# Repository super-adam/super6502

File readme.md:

## 
 - WinCUPL II v1.0 Beta 04/08/2025 (gal-glue-logic folder)
 - KiCad v9.0.6 (kicad folder)
 - KickAssembler v5.25 (src folder)

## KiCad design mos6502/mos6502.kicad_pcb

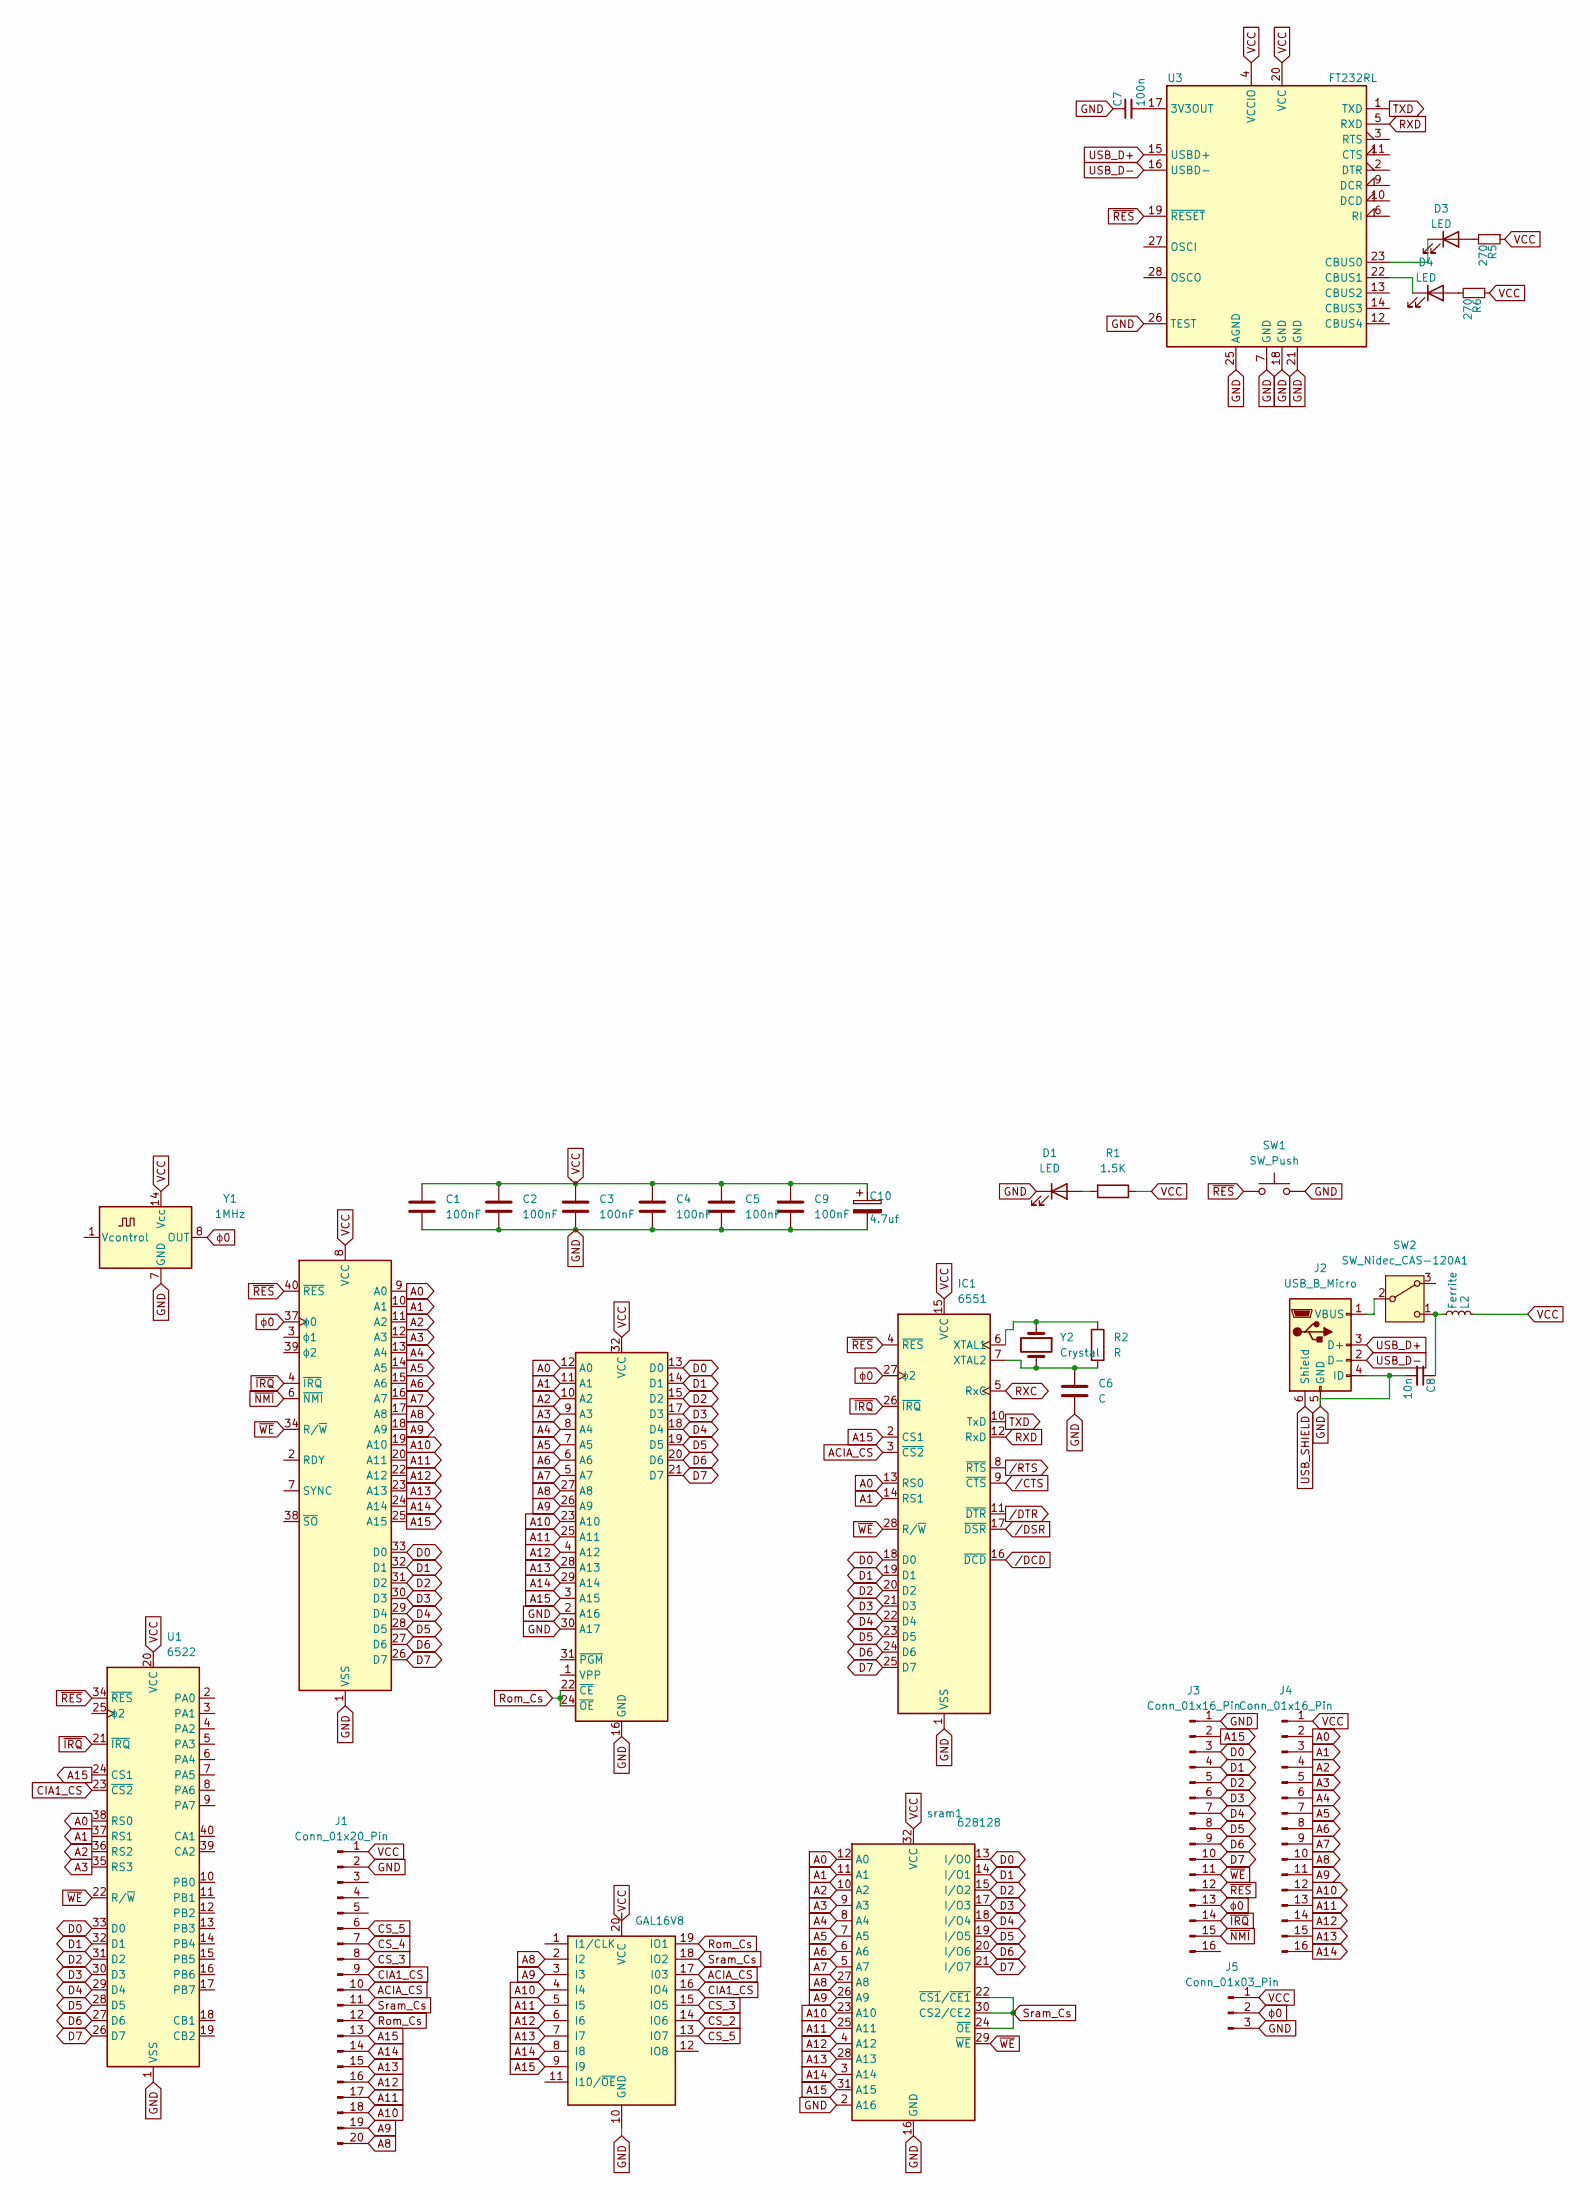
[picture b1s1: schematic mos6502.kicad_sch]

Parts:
C1, C2, C3, C4, C5, C9: 100nF; C_Disc_D5.0mm_W2.5mm_P2.50mm
C6: C; C_0805_2012Metric_Pad1.18x1.45mm_HandSolder
C7: 100n; C_0603_1608Metric
C8: 10n; C_0603_1608Metric
C10: 4.7uf; C_0603_1608Metric
D1: LED; LED_D3.0mm
D3, D4: LED; LED_0805_2012Metric_Pad1.15x1.40mm_HandSolder
IC1: 6551; DIP-28_W15.24mm
J1: Conn_01x20_Pin; PinHeader_1x20_P2.54mm_Vertical
J2: USB_B_Micro; Conn_USBmicro-B_ebay-side_TH
J3, J4: Conn_01x16_Pin; PinHeader_1x16_P2.54mm_Vertical
J5: Conn_01x03_Pin; PinHeader_1x03_P2.54mm_Vertical
L2: Ferrite; L_0603_1608Metric
R1: 1.5K; R_Axial_DIN0207_L6.3mm_D2.5mm_P2.54mm_Vertical
R2: R; R_0805_2012Metric_Pad1.20x1.40mm_HandSolder
R5, R6: 270; R_0603_1608Metric
SW1: SW_Push; SW_Tactile_SKHH_Angled
SW2: SW_Nidec_CAS-120A1; SW_Slide_SPDT_Angled_CK_OS102011MA1Q
U1: 6522; DIP-40_W15.24mm
U3: FT232RL; SSOP-28_5.3x10.2mm_P0.65mm
Y1: 1MHz; Oscillator_DIP-14
Y2: Crystal; Crystal_HC18-U_Vertical
gal1: GAL16V8; DIP-20_W7.62mm
mos1: 6502; DIP-40_W15.24mm
rom1: 27C020; DIP-32_W15.24mm
sram1: 628128; DIP-32_W15.24mm

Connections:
A0: IC1.13 (RS0), J4.2, U1.38 (RS0), mos1.9 (A0), rom1.12 (A0), sram1.12 (A0)
A1: IC1.14 (RS1), J4.3, U1.37 (RS1), mos1.10 (A1), rom1.11 (A1), sram1.11 (A1)
A2: J4.4, U1.36 (RS2), mos1.11 (A2), rom1.10 (A2), sram1.10 (A2)
A3: J4.5, U1.35 (RS3), mos1.12 (A3), rom1.9 (A3), sram1.9 (A3)
A4: J4.6, mos1.13 (A4), rom1.8 (A4), sram1.8 (A4)
A5: J4.7, mos1.14 (A5), rom1.7 (A5), sram1.7 (A5)
A6: J4.8, mos1.15 (A6), rom1.6 (A6), sram1.6 (A6)
A7: J4.9, mos1.16 (A7), rom1.5 (A7), sram1.5 (A7)
A8: J1.20, J4.10, gal1.2 (I2), mos1.17 (A8), rom1.27 (A8), sram1.27 (A8)
A9: J1.19, J4.11, gal1.3 (I3), mos1.18 (A9), rom1.26 (A9), sram1.26 (A9)
A10: J1.18, J4.12, gal1.4 (I4), mos1.19 (A10), rom1.23 (A10), sram1.23 (A10)
A11: J1.17, J4.13, gal1.5 (I5), mos1.20 (A11), rom1.25 (A11), sram1.25 (A11)
A12: J1.16, J4.14, gal1.6 (I6), mos1.22 (A12), rom1.4 (A12), sram1.4 (A12)
A13: J1.15, J4.15, gal1.7 (I7), mos1.23 (A13), rom1.28 (A13), sram1.28 (A13)
A14: J1.14, J4.16, gal1.8 (I8), mos1.24 (A14), rom1.29 (A14), sram1.3 (A14)
A15: IC1.2 (CS1), J1.13, J3.2, U1.24 (CS1), gal1.9 (I9), mos1.25 (A15), rom1.3 (A15), sram1.31 (A15)
ACIA_CS: IC1.3 (~CS2), J1.10, gal1.17 (I03)
CIA1_CS: J1.9, U1.23 (~CS2), gal1.16 (IO4)
CS_2: gal1.14 (IO6)
CS_3: J1.8, gal1.15 (IO5)
CS_4: J1.7
CS_5: J1.6, gal1.13 (IO7)
D0: IC1.18 (D0), J3.3, U1.33 (D0), mos1.33 (D0), rom1.13 (D0), sram1.13 (I/O0)
D1: IC1.19 (D1), J3.4, U1.32 (D1), mos1.32 (D1), rom1.14 (D1), sram1.14 (I/O1)
D2: IC1.20 (D2), J3.5, U1.31 (D2), mos1.31 (D2), rom1.15 (D2), sram1.15 (I/O2)
D3: IC1.21 (D3), J3.6, U1.30 (D3), mos1.30 (D3), rom1.17 (D3), sram1.17 (I/O3)
D4: IC1.22 (D4), J3.7, U1.29 (D4), mos1.29 (D4), rom1.18 (D4), sram1.18 (I/O4)
D5: IC1.23 (D5), J3.8, U1.28 (D5), mos1.28 (D5), rom1.19 (D5), sram1.19 (I/O5)
D6: IC1.24 (D6), J3.9, U1.27 (D6), mos1.27 (D6), rom1.20 (D6), sram1.20 (I/O6)
D7: IC1.25 (D7), J3.10, U1.26 (D7), mos1.26 (D7), rom1.21 (D7), sram1.21 (I/O7)
GND: C1.2, C2.2, C3.2, C4.2, C5.2, C6.2, C7.1, C8.2, C9.2, C10.2, D1.1 (K), IC1.1 (VSS), J1.2, J2.4 (ID), J2.5 (GND), J3.1, J5.3, SW1.2, U1.1 (VSS), U3.7 (GND), U3.18 (GND), U3.21 (GND), U3.25 (AGND), U3.26 (TEST), Y1.7 (GND), gal1.10 (GND), mos1.1 (VSS), mos1.21 (VSS), rom1.2 (A16), rom1.16 (GND), rom1.30 (A17), sram1.2 (A16), sram1.16 (GND)
unnamed: D1.2 (A), R1.2
unnamed: D3.2 (A), R5.2
unnamed: D3.1 (K), U3.23 (CBUS0)
unnamed: D4.2 (A), R6.2
unnamed: D4.1 (K), U3.22 (CBUS1)
unnamed: IC1.6 (XTAL1), R2.1, Y2.1
unnamed: C6.1, IC1.7 (XTAL2), R2.2, Y2.2
unnamed: J2.1 (VBUS), SW2.2 (B)
unnamed 39: C8.1, L2.2, SW2.1 (C); also elsewhere on the board
unnamed: C7.2, U3.17 (3V3OUT)
RXC: IC1.5 (RxC)
RXD: IC1.12 (RxD), U3.5 (RXD)
Rom_Cs: J1.12, gal1.19 (IO1), rom1.22 (~CE), rom1.24 (~OE)
Sram_Cs: J1.11, gal1.18 (IO2), sram1.22 (~CS1/~CE1), sram1.24 (~OE), sram1.30 (CS2/CE2)
TXD: IC1.10 (TxD), U3.1 (TXD)
USB_D+: J2.3 (D+), U3.15 (USBD+)
USB_D-: J2.2 (D-), U3.16 (USBD-)
USB_SHIELD: J2.6 (Shield)
VCC: C1.1, C2.1, C3.1, C4.1, C5.1, C9.1, C10.1, IC1.15 (VCC), J1.1, J4.1, J5.1, L2.1, R1.1, R5.1, R6.1, U1.20 (VCC), U3.4 (VCCIO), U3.20 (VCC), Y1.14 (Vcc), gal1.20 (VCC), mos1.8 (VCC), rom1.32 (VCC), sram1.32 (VCC); also elsewhere on the board
/CTS: IC1.9 (~CTS)
/DCD: IC1.16 (~DCD)
/DSR: IC1.17 (~DSR)
/DTR: IC1.11 (~DTR)
/RTS: IC1.8 (~RTS)
~IRQ: IC1.26 (~IRQ), J3.14, U1.21 (~IRQ), mos1.4 (~IRQ)
~NMI: J3.15, mos1.6 (~NMI)
~RES: IC1.4 (~RES), J3.12, SW1.1, U1.34 (~RES), U3.19 (~RESET), mos1.40 (~RES)
~WE: IC1.28 (R/~W), J3.11, U1.22 (R/~W), mos1.34 (R/~W), sram1.29 (~WE)
ϕ0: IC1.27 (ϕ2), J3.13, J5.2, Y1.8 (OUT), mos1.37 (ϕ0)

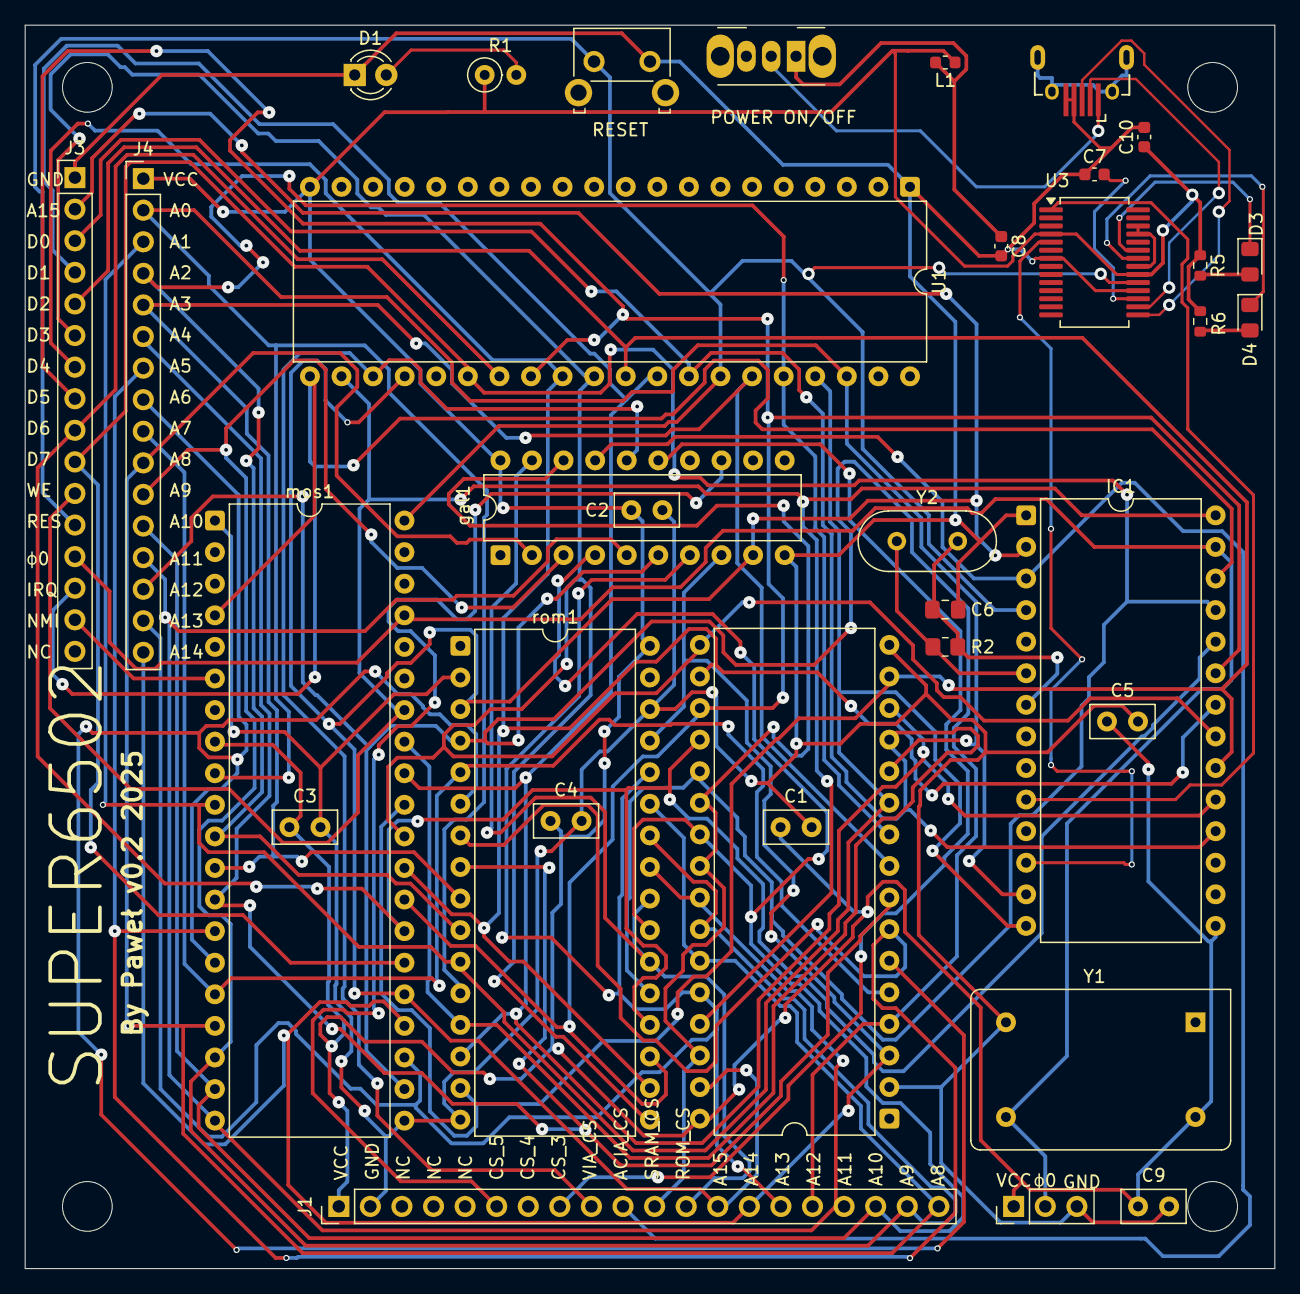
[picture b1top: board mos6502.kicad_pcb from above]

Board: 2 copper layers, 100.5 x 100.0 mm, 34 parts (0 on the bottom side), 51 nets.

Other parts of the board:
L1: Ferrite; L_0603_1608Metric

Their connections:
unnamed 39: L1.2; also elsewhere on the board
VCC: L1.1; also elsewhere on the board

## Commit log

2026-01-27 Added readme
2026-01-27 Added acia_cs signal
2026-01-28 Added KickAssembler kernel code
2026-01-28 Updated tools versions
2026-01-28 Added logo
2026-01-28 Added kicad
2026-01-28 Renamed temp fiolder
2026-01-28 Added datasheets
2026-01-28 ACIA support, initialization and chrout
2026-01-28 updated gitignore
2026-01-28 Glue logic fixes
2026-01-29 Fixes
2026-01-29 Local loopback test
2026-01-29 Local loopback test fixes
